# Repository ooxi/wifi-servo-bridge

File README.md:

# Wifi Servo Bridge 

Sample [firmware](firmware/WifiServoBridge/WifiServoBridge.ino) and
[hardware](hardware/WifiServoBridge) showing of how to utilize ESP32 for driving
servo motors controlled over Wifi.

## Quickstart

```
mc firmware make -C firmware
```

See also [dedicated firmware README](firmware/README.md)

## Usage

* Connect both MCU as well as Servo power to the Wifi Servo Bridge PCB
* Wait until the boot LED is no longer lit up. If the LED starts blinking fast,
  connecting to Wifi causes trouble
* Use the following commands to read and write servo positions. Replace
  `wifi-servo-bridge` with the Wifi Servo Bridge's actual IP (will be displayed
  on serial connection)

```bash
curl -X GET http://wifi-servo-bridge/v2/servo/A/	# Read angle of servo E
curl -X PUT http://wifi-servo-bridge/v2/servo/B/90	# Move servo B to angle 90°
curl -X PUT http://wifi-servo-bridge/v2/servo/E/180	# Move servo E to angle 180°
curl -X PUT http://wifi-servo-bridge/v2/servo/F/0	# Move servo F to angle 0°
```

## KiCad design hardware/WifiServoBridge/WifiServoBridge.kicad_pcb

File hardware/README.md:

# Hardware Errata

## [WifiServoBridge/2021-09-15](WifiServoBridge/2021-09-15)

* `BOOT`-LED is connected to `GPIO6`, which internally is connected to the
  integrated SPI flash, thus unusable for status communication
* Current firmware thus uses `GPIO26` for status communication, which is not
  connected to an LED without a mod

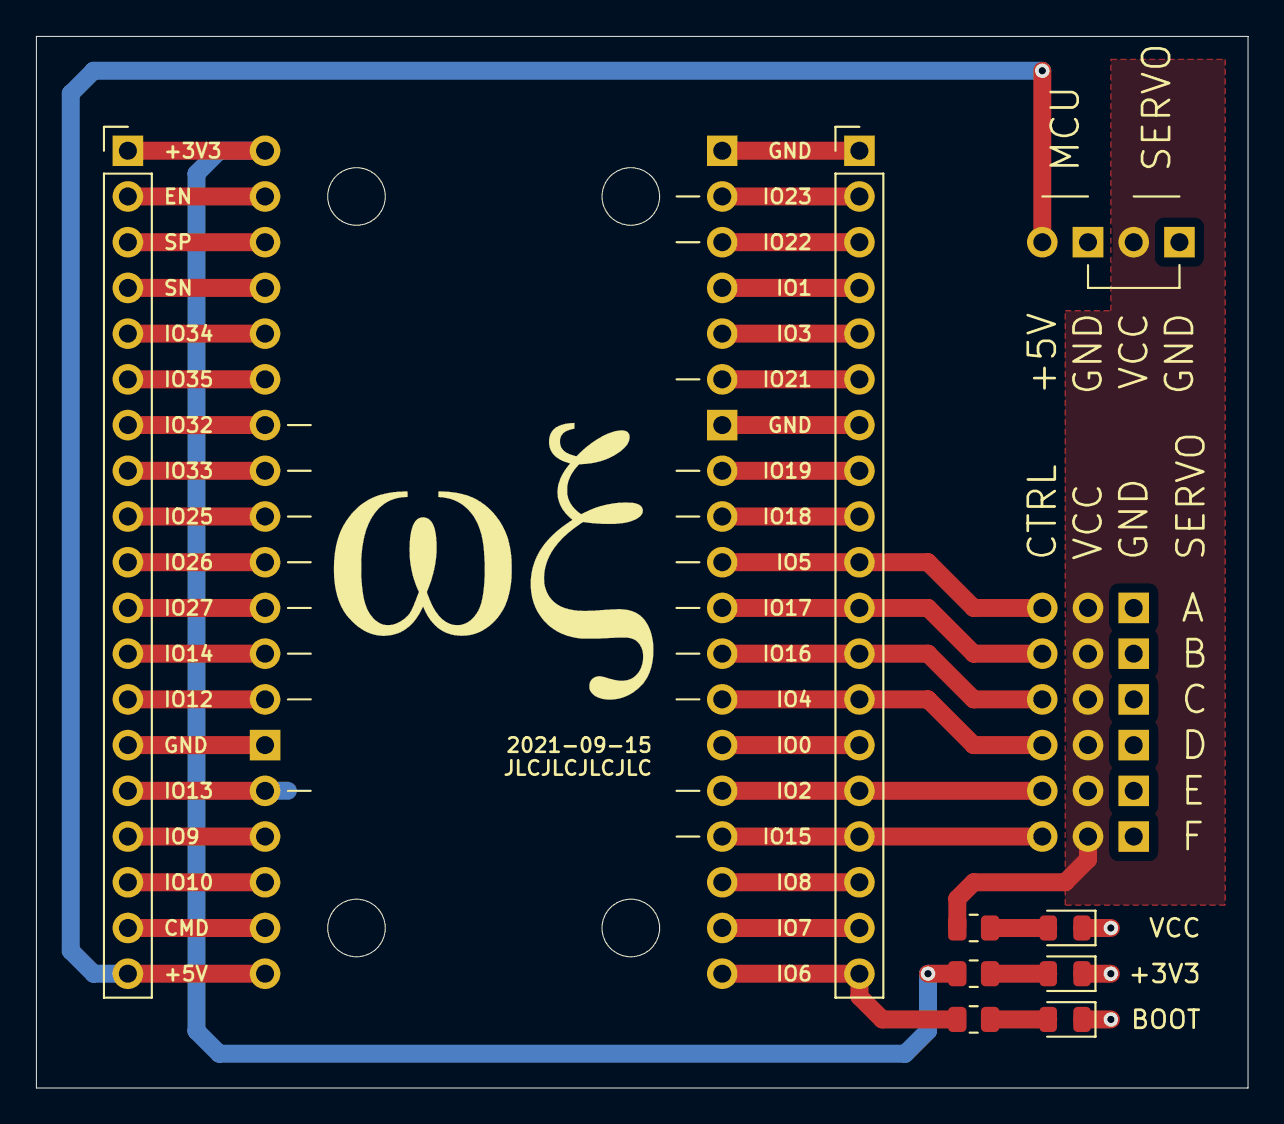
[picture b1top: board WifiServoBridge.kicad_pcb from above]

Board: 2 copper layers, 67.3 x 58.4 mm, 17 parts (0 on the bottom side), 40 nets.

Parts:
D1: VCC; LED_0805_2012Metric
D2: MCU; LED_0805_2012Metric
D3: DEBUG; LED_0805_2012Metric
J1, J2: Conn_01x02; Power Connector
J3, J4: Conn_01x19; PinHeader_1x19_P2.54mm_Vertical
J5, J6, J7, J8, J9, J10: Conn_01x03; Servo Connector
R1: 1000 Ω; R_0805_2012Metric
R2, R3: 660 Ω; R_0805_2012Metric
U1: ESP32NodeMCU; ESP32 NodeMCU

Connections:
DEBUG_LED: J4.19, R3.2, U1.14
MCU_+3V3: J3.1, R2.2, U1.2
MCU_+5V: J2.1, J3.19, U1.3
MCU_CMD: J3.18, U1.7
MCU_EN: J3.2, U1.4
MCU_GND: D1.1, D2.1, D3.1, J1.2, J2.2, J3.14, J4.1, J4.7, J5.3, J6.3, J7.3, J8.3, J9.3, J10.3, U1.1
MCU_GPIO0: J4.14, U1.8
MCU_GPIO1: J4.4, U1.9
MCU_GPIO2: J4.15, J9.1, U1.10
MCU_GPIO3: J4.5, U1.11
MCU_GPIO4: J4.13, J8.1, U1.12
MCU_GPIO5: J4.10, J5.1, U1.13
MCU_GPIO7: J4.18, U1.15
MCU_GPIO8: J4.17, U1.16
MCU_GPIO9: J3.16, U1.17
MCU_GPIO10: J3.17, U1.18
MCU_GPIO12: J3.13, U1.19
MCU_GPIO13: J3.15, U1.20
MCU_GPIO14: J3.12, U1.21
MCU_GPIO15: J4.16, J10.1, U1.22
MCU_GPIO16: J4.12, J7.1, U1.23
MCU_GPIO17: J4.11, J6.1, U1.24
MCU_GPIO18: J4.9, U1.25
MCU_GPIO19: J4.8, U1.26
MCU_GPIO21: J4.6, U1.27
MCU_GPIO22: J4.3, U1.28
MCU_GPIO23: J4.2, U1.29
MCU_GPIO25: J3.9, U1.30
MCU_GPIO26: J3.10, U1.31
MCU_GPIO27: J3.11, U1.32
MCU_GPIO32: J3.7, U1.33
MCU_GPIO33: J3.8, U1.34
MCU_GPIO34: J3.5, U1.35
MCU_GPIO35: J3.6, U1.36
MCU_SN: J3.4, U1.6
MCU_SP: J3.3, U1.5
unnamed: D1.2, R1.1
unnamed: D2.2, R2.1
unnamed: D3.2, R3.1
SERVO_VCC: J1.1, J5.2, J6.2, J7.2, J8.2, J9.2, J10.2, R1.2

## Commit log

2021-09-12 Initial development
    Setup of isolated development environment based on arduino-cli finished.
2021-09-12 Simple servo example
    Provided a sketch which sets the servos to a well known position for manual debugging and as a starting point for modifications which do not need the Wifi part.
2021-09-12 Pin esp32 core version
2021-09-12 Wifi Servo Bridge implementation
2021-09-12 Wifi Servo Bridge Hardware 2021-09-10
    Mounting hole position is not ideal, however I didn't want to increase the PCB size.
2021-09-12 Improved README.md
2021-09-14 Add PDF export to main revisions
2021-09-14 Simplified PWM routing
    Used the physically closed PWM capable pins.
2021-09-14 Add VCC LED and silkscreen labels
    Closes issue #1 and issue #2
2021-09-14 Update GPIO ports to reflect simplified routing
    In order to simplify the routing, physically close PWM capable pins were chosen in 2010491c43cab9126c8b33ba7750f66a60a62bff. This change reflects the physical properties of board 2021-10-14 in firmwa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
2021-09-15 `MCU_GND' and `SERVO_GND' must be connected on board
    Since the serve control line is relative to the servo ground potential, MCU and servo ground must be on the same potential.
2021-09-15 Improved optics by routing +5V as well as +3V3 on bottom
2021-09-15 Production data of PCB order
2021-09-15 Drill files have to be exported separately from plotting Gerber
2021-09-30 API v2
    Replaced numeric servo index by textual servo name.
    Warning: Firmware not yet verified on hardware
2021-09-30 Mock API implementation for GUI development
2021-11-25 Fix broken link
2021-11-25 Add CI using GitHub Actions
2022-05-29 Add periodic rebuild
2022-08-25 Fix minor API documentation mistake in README
2022-08-26 Added hardware errata
2022-08-26 WifiServoBrdige Access Point support
    Using a compile time switch, one can now change the behaviour of WifiServoBridge from Wifi Client to Wifi Access Point
2022-11-20 Add CI badge to README.md
2022-12-17 Update to actions/checkout@v3
2022-12-17 Run CI on all branches
2023-06-11 Improved documentation
2023-06-24 ci test
